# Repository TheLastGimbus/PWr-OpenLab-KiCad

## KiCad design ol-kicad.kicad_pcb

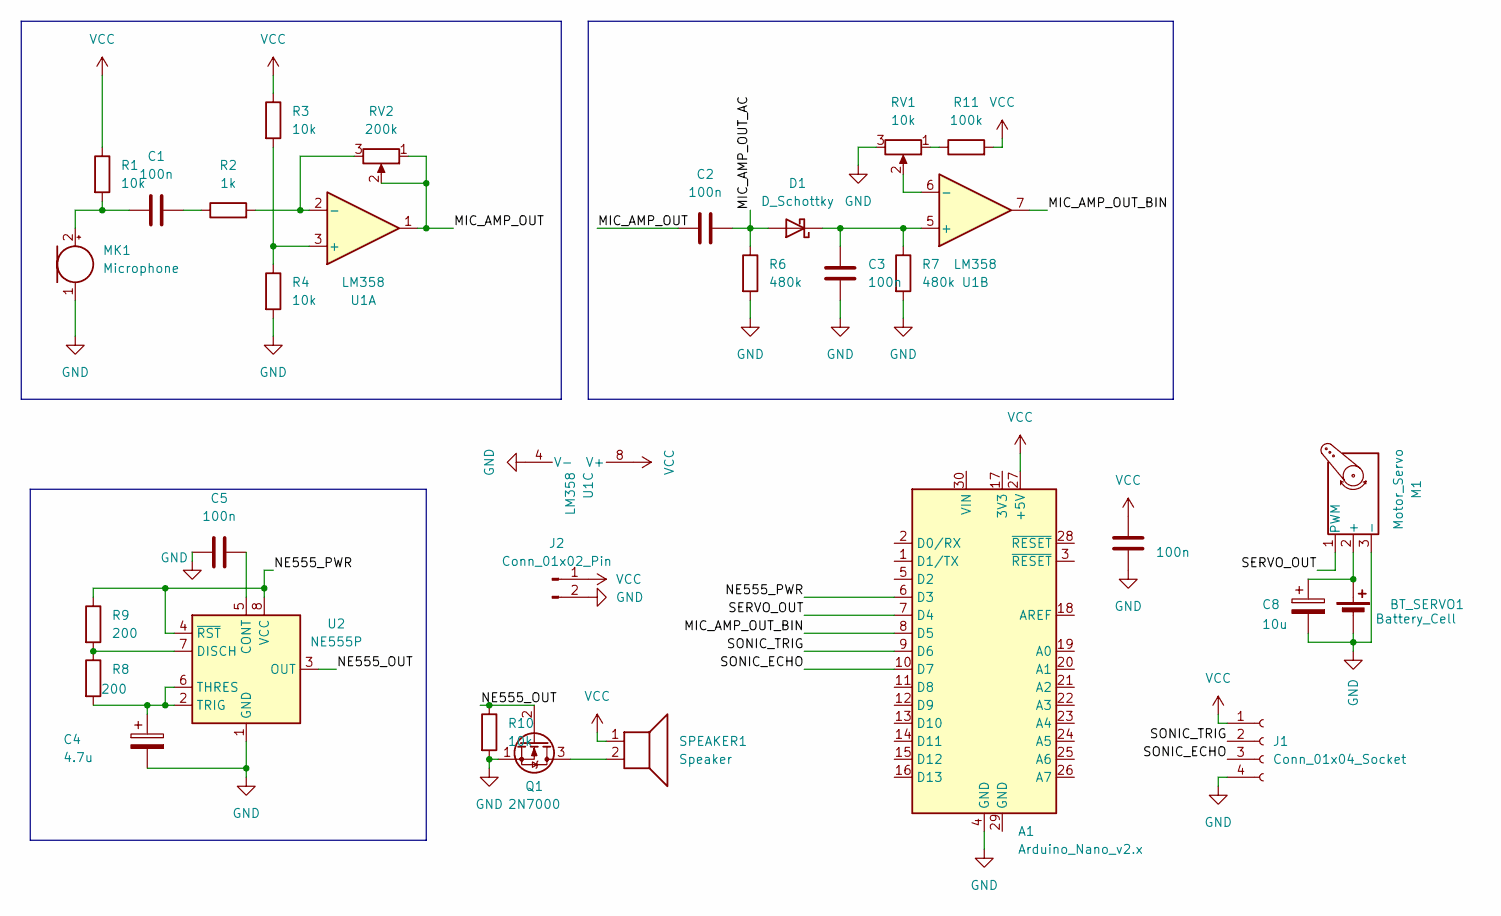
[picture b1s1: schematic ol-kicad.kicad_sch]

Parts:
A1: Arduino_Nano_v2.x; Arduino_Nano
BT_SERVO1: Battery_Cell; PinHeader_1x02_P2.54mm_Vertical
C1, C2, C3, C6: 100n; C_Disc_D5.0mm_W2.5mm_P2.50mm
C4: 4.7u; CP_Radial_D5.0mm_P2.50mm
C5: 100n; C_Disc_D5.0mm_W2.5mm_P5.00mm
C8: 10u; CP_Radial_D10.0mm_P5.00mm
D1: D_Schottky; D_DO-35_SOD27_P7.62mm_Horizontal
J1: Conn_01x04_Socket
J2: Conn_01x02_Pin; PinHeader_1x02_P2.54mm_Vertical
M1: Motor_Servo; PinHeader_1x03_P2.54mm_Vertical
MK1: Microphone; PinHeader_1x02_P2.54mm_Vertical
Q1: 2N7000; TO-92_Inline_Wide
R1, R3, R4, R10: 10k; R_Axial_DIN0207_L6.3mm_D2.5mm_P7.62mm_Horizontal
R2: 1k; R_Axial_DIN0207_L6.3mm_D2.5mm_P7.62mm_Horizontal
R6, R7: 480k; R_Axial_DIN0207_L6.3mm_D2.5mm_P7.62mm_Horizontal
R8, R9: 200; R_Axial_DIN0207_L6.3mm_D2.5mm_P7.62mm_Horizontal
R11: 100k; R_Axial_DIN0207_L6.3mm_D2.5mm_P7.62mm_Horizontal
RV1: 10k; Potentiometer_Runtron_RM-065_Vertical
RV2: 200k; Potentiometer_Runtron_RM-065_Vertical
SPEAKER1: Speaker; PinHeader_1x02_P2.54mm_Vertical
U1: LM358; DIP-8_W7.62mm
U2: NE555P; DIP-8_W7.62mm

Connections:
/MIC_AMP_OUT: C2.1, RV2.1, RV2.2, U1.1
/MIC_AMP_OUT_AC: C2.2, D1.2 (A), R6.1
/MIC_AMP_OUT_BIN: A1.8 (D5), U1.7
/NE555_OUT: Q1.2 (G), R10.1, U2.3 (OUT)
/NE555_PWR: A1.6 (D3), R9.1, U2.4 (~RST), U2.8 (VCC)
/SERVO_OUT: A1.7 (D4), M1.1 (PWM)
/SONIC_ECHO: A1.10 (D7), J1.3
/SONIC_TRIG: A1.9 (D6), J1.2
GND: A1.4 (GND), BT_SERVO1.2 (-), C3.2, C4.2, C5.1, C6.2, C8.2, J1.4, J2.2, M1.3 (-), MK1.1 (-), Q1.1 (S), R4.2, R6.2, R7.2, R10.2, RV1.3, U1.4 (V-), U2.1 (GND)
unnamed: BT_SERVO1.1 (+), C8.1, M1.2 (+)
unnamed: C1.1, R2.1
unnamed: C3.1, D1.1 (K), R7.1, U1.5 (+)
unnamed: C1.2, MK1.2 (+), R1.2
unnamed: Q1.3 (D), SPEAKER1.2
unnamed: R11.1, RV1.1
unnamed: R3.2, R4.1, U1.3 (+)
unnamed: R2.2, RV2.3, U1.2 (-)
unnamed: RV1.2, U1.6 (-)
unnamed: C5.2, U2.5 (CONT)
unnamed: R8.1, R9.2, U2.7 (DISCH)
unnamed: C4.1, R8.2, U2.2 (TRIG), U2.6 (THRES)
VCC: A1.27 (+5V), C6.1, J1.1, J2.1, R1.1, R3.1, R11.2, SPEAKER1.1, U1.8 (V+)

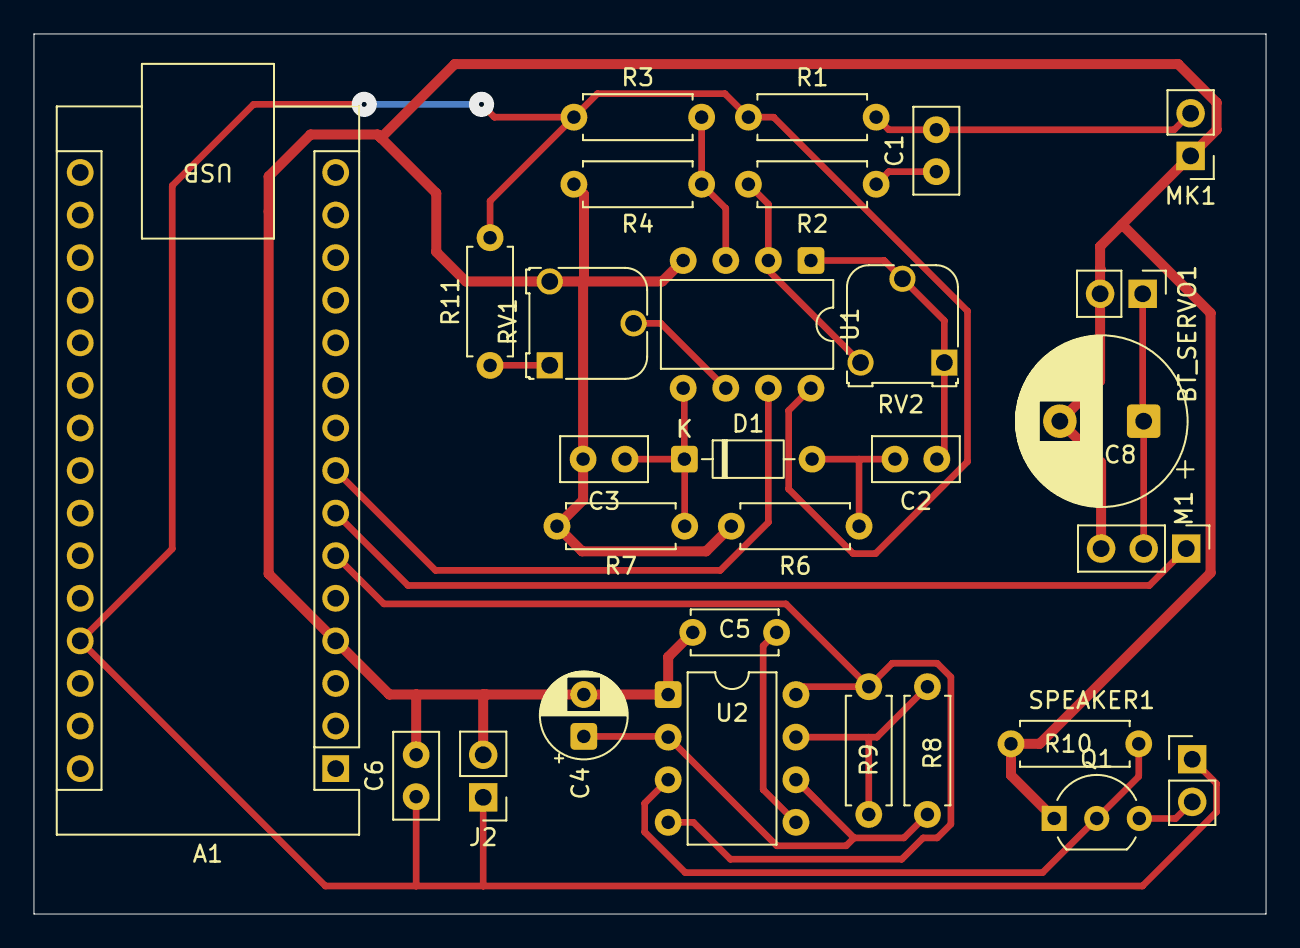
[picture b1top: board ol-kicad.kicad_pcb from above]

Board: 2 copper layers, 73.5 x 52.5 mm, 29 parts (0 on the bottom side), 20 nets.

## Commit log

2026-04-14 first
2026-04-19 platformio
2026-04-19 klaskanie
